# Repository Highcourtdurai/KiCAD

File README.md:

# KiCAD
Contains 555 timer circuit and basic circuits

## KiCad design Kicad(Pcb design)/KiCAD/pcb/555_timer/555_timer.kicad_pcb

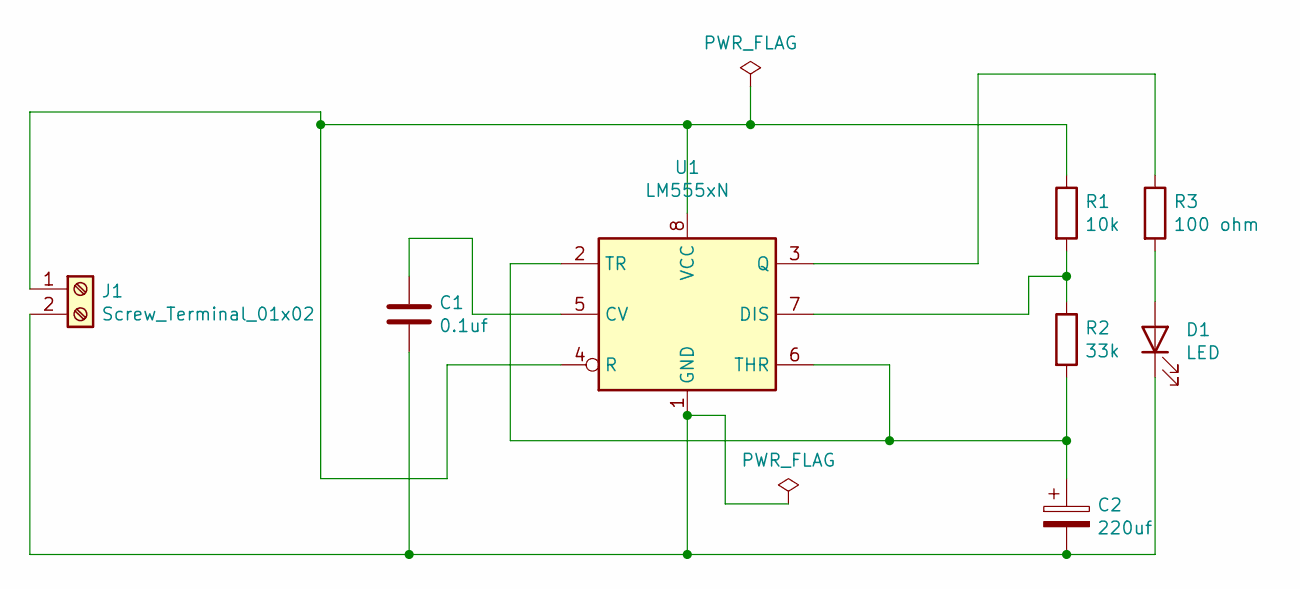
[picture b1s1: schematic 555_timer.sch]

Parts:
C1: 0.1uf; C_Disc_D9.0mm_W5.0mm_P7.50mm
C2: 220uf; CP_Radial_D7.5mm_P2.50mm
D1: LED; LED_D3.0mm
J1: Screw_Terminal_01x02; PhoenixContact_MCV_1,5_2-G-3.5_1x02_P3.50mm_Vertical
R1: 10k; R_Axial_DIN0204_L3.6mm_D1.6mm_P7.62mm_Horizontal
R2: 33k; R_Axial_DIN0204_L3.6mm_D1.6mm_P7.62mm_Horizontal
R3: 100 ohm; R_Axial_DIN0204_L3.6mm_D1.6mm_P7.62mm_Horizontal
U1: LM555xN; DIP-8_W7.62mm_Socket

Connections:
unnamed: C1.1, U1.5 (CV)
unnamed: C1.2, C2.2, D1.1 (K), J1.2, U1.1 (GND)
unnamed: C2.1, R2.2, U1.2 (TR), U1.6 (THR)
unnamed: D1.2 (A), R3.2
unnamed: J1.1, R1.1, U1.4 (R), U1.8 (VCC)
unnamed: R1.2, R2.1, U1.7 (DIS)
unnamed: R3.1, U1.3 (Q)

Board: 2 copper layers, 8 parts (0 on the bottom side), 7 nets, no tracks yet.

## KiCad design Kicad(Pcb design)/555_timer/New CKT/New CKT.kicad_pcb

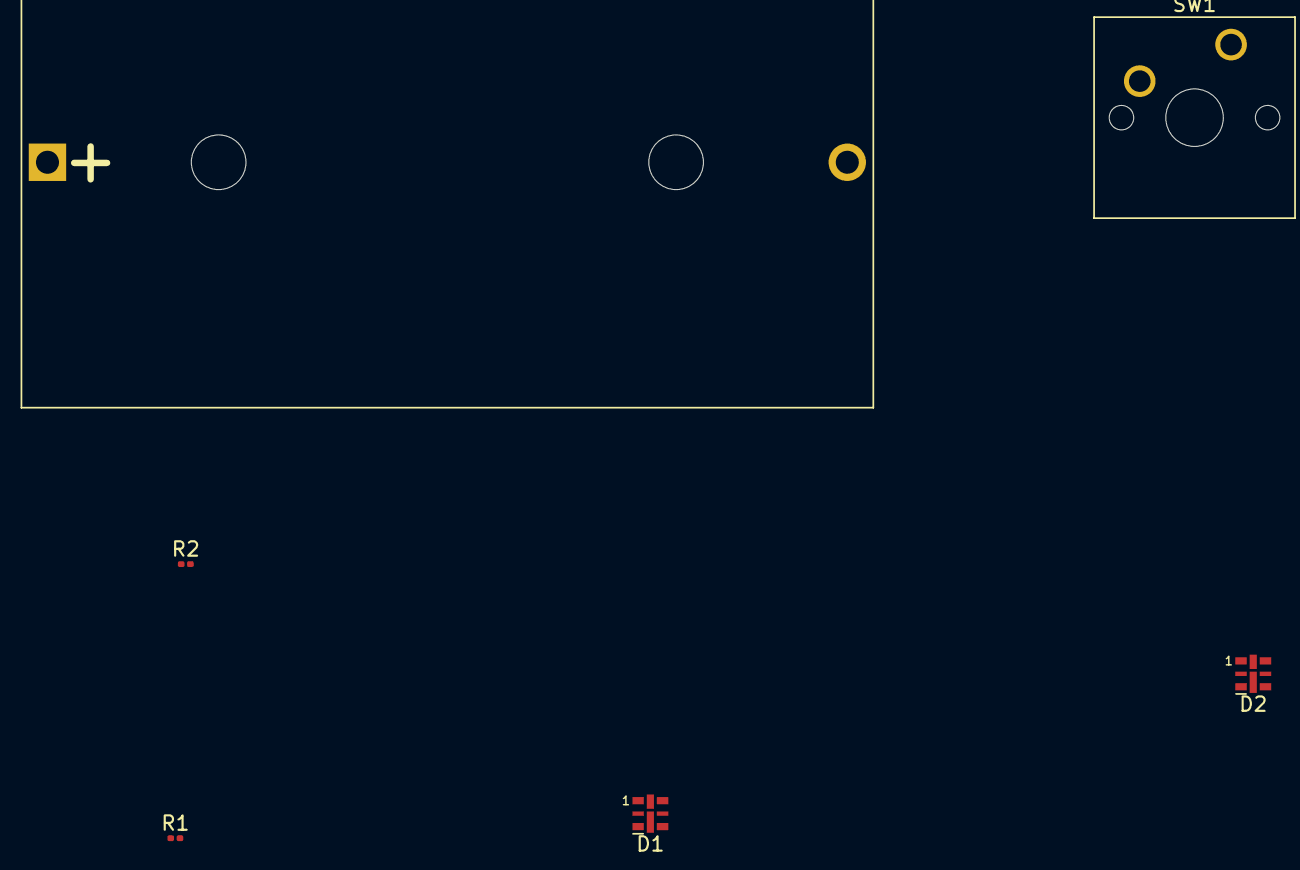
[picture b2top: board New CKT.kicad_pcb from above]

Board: 2 copper layers, 6 parts (0 on the bottom side), 5 nets, no tracks yet.

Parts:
BT1: 5V; BatteryHolder_Bulgin_BX0036_1xC
D1, D2: LED; LED-APA102-2020
R1, R2: 100 ohm; R_0201_0603Metric
SW1: ON/OFF; SW_Cherry_MX_1.00u_PCB

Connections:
unnamed: BT1.1, SW1.1
unnamed: BT1.2, D1.1, D2.1
unnamed: D1.2, R1.2
unnamed: D2.2, R2.2
unnamed: R1.1, R2.1, SW1.2
